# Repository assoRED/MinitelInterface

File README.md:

# MinitelInterface

Desinged by [Ybalrid](https://github.com/Ybalrid/)

Minitel to RS232 converter circuit (based on a MAX232 IC). Can literally be built with random stuff laying around at RED :wink:

Repository contains a KiCad project to build the board. http://pafgadget.free.fr/bidouillages/minitel/minittl.png

This is based on this circuit from paf gadget, but some filtering capacitor have been muntzed out :open_mouth: . Should be just fine... :wink:

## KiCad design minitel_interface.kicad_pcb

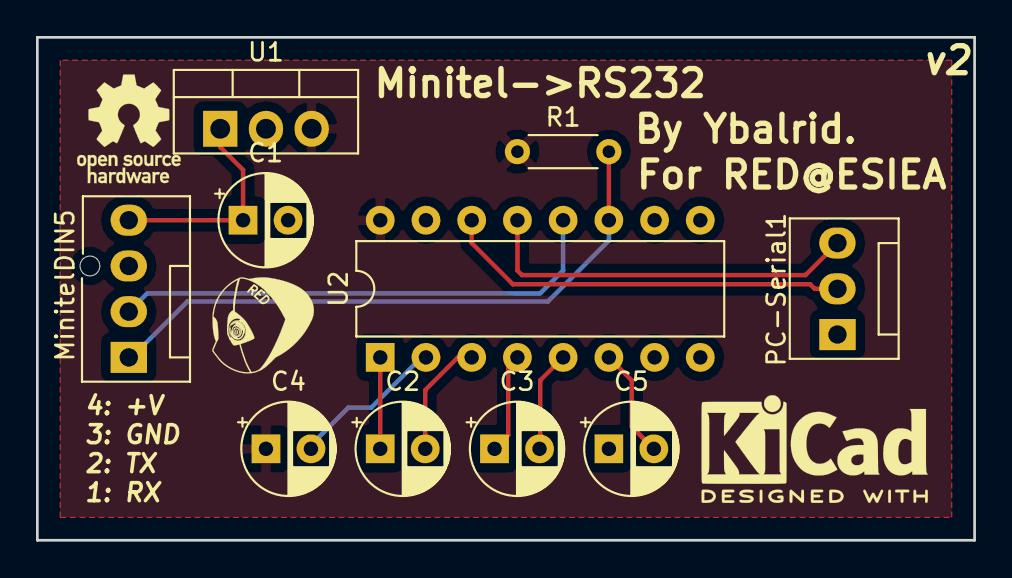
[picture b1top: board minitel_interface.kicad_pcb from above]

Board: 2 copper layers, 52.1 x 27.9 mm, 10 parts (0 on the bottom side), 13 nets.

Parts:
C1, C2, C3, C4, C5: 100nF; CP_Radial_D5.0mm_P2.50mm
MinitelDIN5: DIN-5; FanPinHeader_1x04_P2.54mm_Vertical
PC-Serial1: DB9_Female; FanPinHeader_1x03_P2.54mm_Vertical
R1: 10k; R_Axial_DIN0204_L3.6mm_D1.6mm_P5.08mm_Horizontal
U1: L7805; TO-220-3_Vertical
U2: MAX232; DIP-16_W7.62mm

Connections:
+12V: C1.1, MinitelDIN5.4, U1.1
GND: C1.2, C5.1, MinitelDIN5.3, PC-Serial1.1, U1.2, U2.15
unnamed: C2.1, U2.1
unnamed: C2.2, U2.3
unnamed: C3.1, U2.4
unnamed: C3.2, U2.5
unnamed: C4.2, U2.2
unnamed: C5.2, U2.6
unnamed: MinitelDIN5.1, R1.2, U2.11
unnamed: MinitelDIN5.2, U2.12
unnamed: PC-Serial1.2, U2.14
unnamed: PC-Serial1.3, U2.13
REG_5V: C4.1, R1.1, U1.3, U2.16

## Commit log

2018-09-20 Add kicad project
2018-09-20 Create LICENSE
2018-10-06 Fix confusion on two pins on the MAX232
    (original board requreid bodge wire)
